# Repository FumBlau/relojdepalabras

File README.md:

# relojdepalabras
nuestro wordclock, de sobremesa o de pared

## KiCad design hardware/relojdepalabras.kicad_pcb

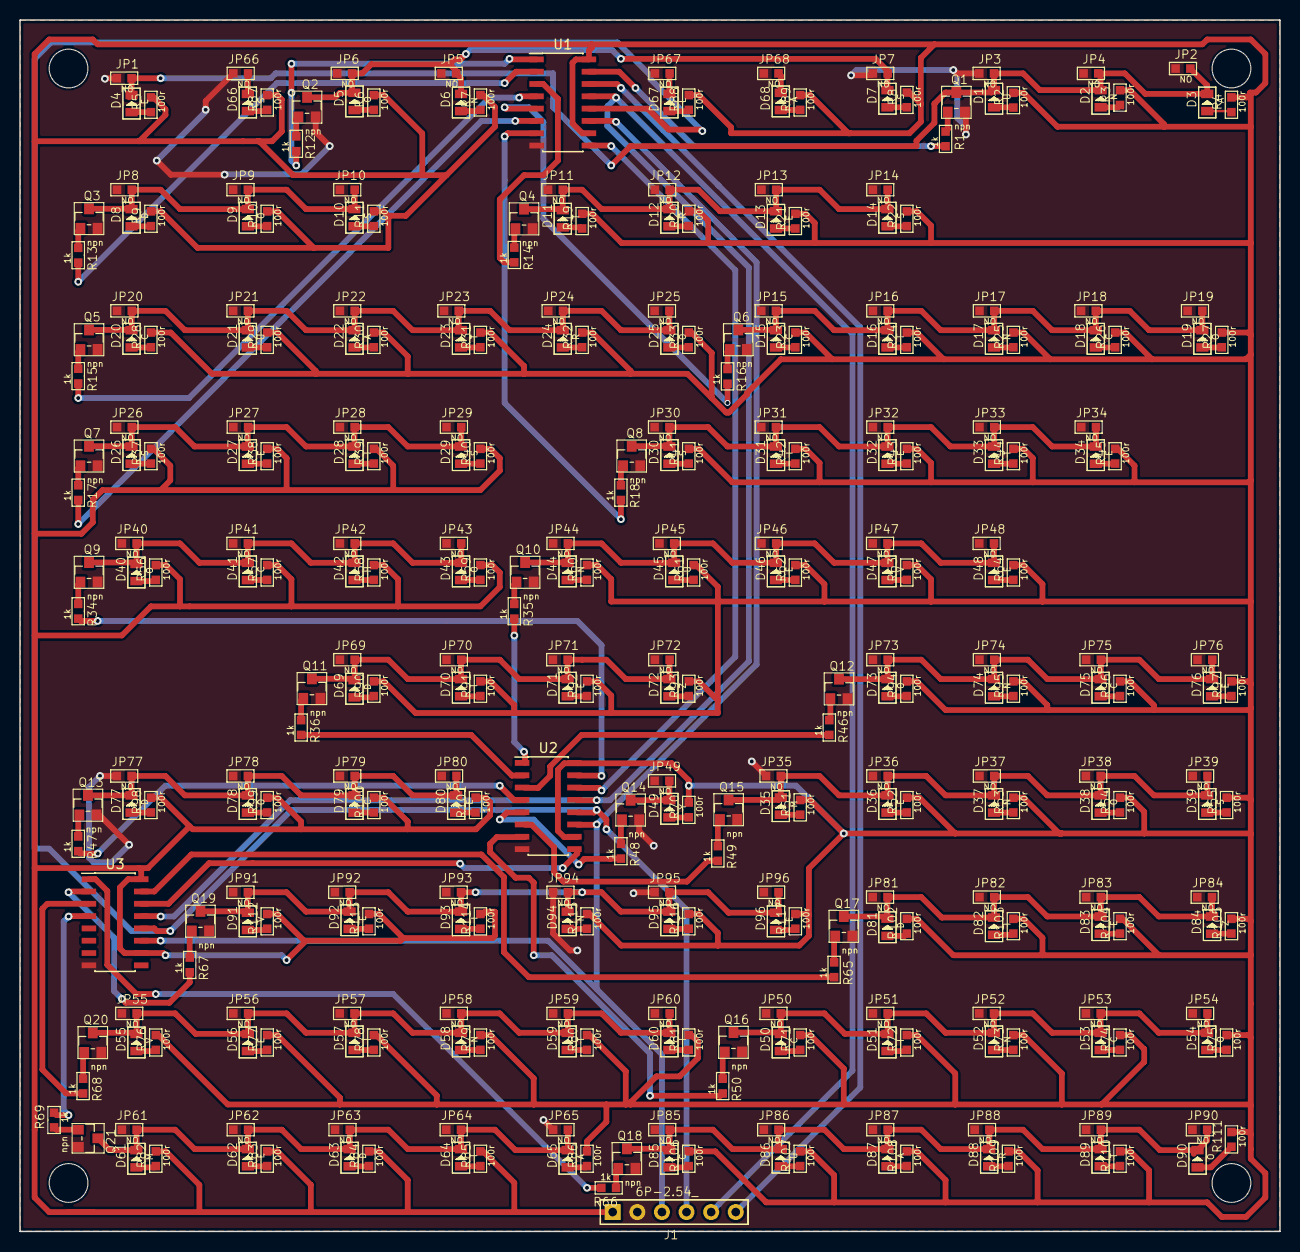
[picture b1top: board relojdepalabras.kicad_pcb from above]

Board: 2 copper layers, 130.0 x 125.0 mm, 334 parts (0 on the bottom side), 170 nets.

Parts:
D1, D21, D45, D86: U; LED-0805
D2, D6, D17, D37, D44, D52, D58, D74, D94: N; LED-0805
D3, D22, D65, D68, D87: A; LED-0805
D4, D13, D27, D32, D34, D36, D46, D48, D56, D62, D71, D76, D80, D83, D92, D96: E; LED-0805
D5, D9, D19, D25, D38, D40, D43, D54, D73, D78, D90: O; LED-0805
D7, D10, D14, D26, D29, D30, D39, D66: S; LED-0805
D8, D63, D69, D77, D81: D; LED-0805
D11, D23, D33, D59, D89, D95: T; LED-0805
D12, D24, D88: R; LED-0805
D15, D18, D20, D41, D50, D53, D75, D79, D85: C; LED-0805
D16, D28, D31, D51, D57, D60, D64, D70, D82, D93: I; LED-0805
D35, D61: M; LED-0805
D42: H; LED-0805
D47, D55, D91: V; LED-0805
D49: Y; LED-0805
D67: L; LED-0805
D72, D84: Z; LED-0805
J1: 6P-2.54_; H6-2.54
JP1, JP2, JP3, JP4, JP5, JP6, JP7, JP8, JP9, JP10, JP11, JP12, JP13, JP14, JP15, JP16, JP17, JP18, JP19, JP20, JP21, JP22, JP23, JP24, JP25, JP26, JP27, JP28, JP29, JP30, JP31, JP32, JP33, JP34, JP35, JP36, JP37, JP38, JP39, JP40, JP41, JP42, JP43, JP44, JP45, JP46, JP47, JP48, JP49, JP50, JP51, JP52, JP53, JP54, JP55, JP56, JP57, JP58, JP59, JP60, JP61, JP62, JP63, JP64, JP65, JP66, JP67, JP68, JP69, JP70, JP71, JP72, JP73, JP74, JP75, JP76, JP77, JP78, JP79, JP80, JP81, JP82, JP83, JP84, JP85, JP86, JP87, JP88, JP89, JP90, JP91, JP92, JP93, JP94, JP95, JP96: NO; R0603
Q1, Q2, Q3, Q4, Q5, Q6, Q7, Q8, Q9, Q10, Q11, Q12, Q13, Q14, Q15, Q16, Q17, Q18, Q19, Q20, Q21: npn; SOT-23
R1, R12, R13, R14, R15, R16, R17, R18, R34, R35, R36, R46, R47, R48, R49, R50, R65, R66, R67, R68, R69: 1k; R0603
R2, R3, R4, R5, R6, R7, R8, R9, R10, R11, R19, R20, R21, R22, R23, R24, R25, R26, R27, R28, R29, R30, R31, R32, R33, R37, R38, R39, R40, R41, R42, R43, R44, R45, R51, R52, R53, R54, R55, R56, R57, R58, R59, R60, R61, R62, R63, R64, R70, R71, R72, R73, R74, R75, R76, R77, R78, R79, R80, R81, R82, R83, R84, R85, R86, R87, R88, R89, R90, R91, R92, R93, R94, R95, R96, R97, R98, R99, R100, R101, R102, R103, R104, R105, R106, R107, R108, R109, R110, R111, R112, R113, R114, R115, R116, R117: 100r; R0603
U1, U2, U3: 74HC595; SOIC-16_3.9x9.9mm_Pitch1.27mm

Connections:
+5V: J1.1, R2.1, R3.1, R4.1, R5.1, R6.1, R7.1, R8.1, R9.1, R10.1, R11.1, R19.1, R20.1, R21.1, R22.1, R23.1, R24.1, R25.1, R26.1, R27.1, R28.1, R29.1, R30.1, R31.1, R32.1, R33.1, R37.1, R38.1, R39.1, R40.1, R41.1, R42.1, R43.1, R44.1, R45.1, R51.1, R52.1, R53.1, R54.1, R55.1, R56.1, R57.1, R58.1, R59.1, R60.1, R61.1, R62.1, R63.1, R64.1, R70.1, R71.1, R72.1, R73.1, R74.1, R75.1, R76.1, R77.1, R78.1, R79.1, R80.1, R81.1, R82.1, R83.1, R84.1, R85.1, R86.1, R87.1, R88.1, R89.1, R90.1, R91.1, R92.1, R93.1, R94.1, R95.1, R96.1, R97.1, R98.1, R99.1, R100.1, R101.1, R102.1, R103.1, R104.1, R105.1, R106.1, R107.1, R108.1, R109.1, R110.1, R111.1, R112.1, R113.1, R114.1, R115.1, R116.1, R117.1, U1.10, U1.16, U2.10, U2.16, U3.10, U3.16
/!sh/ld: J1.4, U1.12, U2.12, U3.12
/datos: J1.6, U1.14
/enable: J1.5, U1.13, U2.13, U3.13
/reloj: J1.3, U1.11, U2.11, U3.11
CINCO: D15.-, D16.-, D17.-, D18.-, D19.-, JP15.1, JP16.1, JP17.1, JP18.1, JP19.1, Q6.3
CUATRO: D20.-, D21.-, D22.-, D23.-, D24.-, D25.-, JP20.1, JP21.1, JP22.1, JP23.1, JP24.1, JP25.1, Q5.3
DIEZ: D69.-, D70.-, D71.-, D72.-, JP69.1, JP70.1, JP71.1, JP72.1, Q11.3
DOCE: D77.-, D78.-, D79.-, D80.-, JP77.1, JP78.1, JP79.1, JP80.1, Q13.3
DOS: D8.-, D9.-, D10.-, JP8.1, JP9.1, JP10.1, Q3.3
E/UNA: D1.-, D2.-, D3.-, D4.-, JP1.1, JP2.1, JP3.1, JP4.1, Q1.3
GND: J1.2, JP1.2, JP2.2, JP3.2, JP4.2, JP5.2, JP6.2, JP7.2, JP8.2, JP9.2, JP10.2, JP11.2, JP12.2, JP13.2, JP14.2, JP15.2, JP16.2, JP17.2, JP18.2, JP19.2, JP20.2, JP21.2, JP22.2, JP23.2, JP24.2, JP25.2, JP26.2, JP27.2, JP28.2, JP29.2, JP30.2, JP31.2, JP32.2, JP33.2, JP34.2, JP35.2, JP36.2, JP37.2, JP38.2, JP39.2, JP40.2, JP41.2, JP42.2, JP43.2, JP44.2, JP45.2, JP46.2, JP47.2, JP48.2, JP49.2, JP50.2, JP51.2, JP52.2, JP53.2, JP54.2, JP55.2, JP56.2, JP57.2, JP58.2, JP59.2, JP60.2, JP61.2, JP62.2, JP63.2, JP64.2, JP65.2, JP66.2, JP67.2, JP68.2, JP69.2, JP70.2, JP71.2, JP72.2, JP73.2, JP74.2, JP75.2, JP76.2, JP77.2, JP78.2, JP79.2, JP80.2, JP81.2, JP82.2, JP83.2, JP84.2, JP85.2, JP86.2, JP87.2, JP88.2, JP89.2, JP90.2, JP91.2, JP92.2, JP93.2, JP94.2, JP95.2, JP96.2, Q1.2, Q2.2, Q3.2, Q4.2, Q5.2, Q6.2, Q7.2, Q8.2, Q9.2, Q10.2, Q11.2, Q12.2, Q13.2, Q14.2, Q15.2, Q16.2, Q17.2, Q18.2, Q19.2, Q20.2, Q21.2, U1.8, U2.8, U3.8
MENOS: D35.-, D36.-, D37.-, D38.-, D39.-, JP35.1, JP36.1, JP37.1, JP38.1, JP39.1, Q15.3
NUEVE: D44.-, D45.-, D46.-, D47.-, D48.-, JP44.1, JP45.1, JP46.1, JP47.1, JP48.1, Q10.3
unnamed: D1.+, R2.2
unnamed: D2.+, R3.2
unnamed: D3.+, R4.2
unnamed: D4.+, R5.2
unnamed: D5.+, R6.2
unnamed: D6.+, R7.2
unnamed: D7.+, R8.2
unnamed: D8.+, R9.2
unnamed: D9.+, R10.2
unnamed: D10.+, R11.2
unnamed: D11.+, R19.2
unnamed: D12.+, R20.2
unnamed: D13.+, R21.2
unnamed: D14.+, R22.2
unnamed: D15.+, R23.2
unnamed: D16.+, R24.2
unnamed: D17.+, R25.2
unnamed: D18.+, R26.2
unnamed: D19.+, R27.2
unnamed: D20.+, R28.2
unnamed: D21.+, R29.2
unnamed: D22.+, R30.2
unnamed: D23.+, R31.2
unnamed: D24.+, R32.2
unnamed: D25.+, R33.2
unnamed: D26.+, R37.2
unnamed: D27.+, R38.2
unnamed: D28.+, R39.2
unnamed: D29.+, R40.2
unnamed: D30.+, R41.2
unnamed: D31.+, R42.2
unnamed: D32.+, R43.2
unnamed: D33.+, R44.2
unnamed: D34.+, R45.2
unnamed: D35.+, R51.2
unnamed: D36.+, R52.2
unnamed: D37.+, R53.2
unnamed: D38.+, R54.2
unnamed: D39.+, R55.2
unnamed: D40.+, R56.2
unnamed: D41.+, R57.2
unnamed: D42.+, R58.2
unnamed: D43.+, R59.2
unnamed: D44.+, R60.2
unnamed: D45.+, R61.2
unnamed: D46.+, R62.2
unnamed: D47.+, R63.2
unnamed: D48.+, R64.2
unnamed: D49.+, R70.2
unnamed: D50.+, R71.2
unnamed: D51.+, R72.2
unnamed: D52.+, R73.2
unnamed: D53.+, R74.2
unnamed: D54.+, R75.2
unnamed: D55.+, R76.2
unnamed: D56.+, R77.2
unnamed: D57.+, R78.2
unnamed: D58.+, R79.2
unnamed: D59.+, R80.2
unnamed: D60.+, R81.2
unnamed: D61.+, R82.2
unnamed: D62.+, R83.2
unnamed: D63.+, R84.2
unnamed: D64.+, R85.2
unnamed: D65.+, R86.2
unnamed: D66.+, R87.2
unnamed: D66.-, JP66.1
unnamed: D67.+, R88.2
unnamed: D67.-, JP67.1
unnamed: D68.+, R89.2
unnamed: D68.-, JP68.1
unnamed: D69.+, R90.2
unnamed: D70.+, R91.2
unnamed: D71.+, R92.2
unnamed: D72.+, R93.2
unnamed: D73.+, R94.2
unnamed: D74.+, R95.2
unnamed: D75.+, R96.2
unnamed: D76.+, R97.2
unnamed: D77.+, R98.2
unnamed: D78.+, R99.2
unnamed: D79.+, R100.2
unnamed: D80.+, R101.2
unnamed: D81.+, R102.2
unnamed: D82.+, R103.2
unnamed: D83.+, R104.2
unnamed: D84.+, R105.2
unnamed: D85.+, R106.2
unnamed: D86.+, R107.2
unnamed: D87.+, R108.2
unnamed: D88.+, R109.2
unnamed: D89.+, R110.2
unnamed: D90.+, R111.2
unnamed: D91.+, R112.2
unnamed: D92.+, R113.2
unnamed: D93.+, R114.2
unnamed: D94.+, R115.2
unnamed: D95.+, R116.2
unnamed: D96.+, R117.2
unnamed: Q1.1, R1.2
unnamed: Q2.1, R12.2
unnamed: Q3.1, R13.2
unnamed: Q4.1, R14.2
unnamed: Q5.1, R15.2
unnamed: Q6.1, R16.2
unnamed: Q7.1, R17.2
unnamed: Q8.1, R18.2
unnamed: Q9.1, R34.2
unnamed: Q10.1, R35.2
unnamed: Q11.1, R36.2
unnamed: Q12.1, R46.2
unnamed: Q13.1, R47.2
unnamed: Q14.1, R48.2
unnamed: Q15.1, R49.2
unnamed: Q16.1, R50.2
unnamed: Q17.1, R65.2
unnamed: Q18.1, R66.2
unnamed: Q19.1, R67.2
unnamed: Q20.1, R68.2
unnamed: Q21.1, R69.2
unnamed: R1.1, U1.15
unnamed: R12.1, U1.1
unnamed: R13.1, U1.2
unnamed: R14.1, U1.3
unnamed: R15.1, U1.4
unnamed: R16.1, U1.5
unnamed: R17.1, U1.6
unnamed: R18.1, U1.7
unnamed: R34.1, U2.15
unnamed: R35.1, U2.1
unnamed: R36.1, U2.2
unnamed: R46.1, U2.3
unnamed: R47.1, U2.4
unnamed: R48.1, U2.5
unnamed: R49.1, U2.6
unnamed: R50.1, U2.7
unnamed: R65.1, U3.15
unnamed: R66.1, U3.1
unnamed: R67.1, U3.2
unnamed: R68.1, U3.3
unnamed: R69.1, U3.4
unnamed: U1.9, U2.14
unnamed: U2.9, U3.14
OCHO: D40.-, D41.-, D42.-, D43.-, JP40.1, JP41.1, JP42.1, JP43.1, Q9.3
ONCE: D73.-, D74.-, D75.-, D76.-, JP73.1, JP74.1, JP75.1, JP76.1, Q12.3
SEIS: D26.-, D27.-, D28.-, D29.-, JP26.1, JP27.1, JP28.1, JP29.1, Q7.3
SIETE: D30.-, D31.-, D32.-, D33.-, D34.-, JP30.1, JP31.1, JP32.1, JP33.1, JP34.1, Q8.3
SonLas: D5.-, D6.-, D7.-, JP5.1, JP6.1, JP7.1, Q2.3
TRES: D11.-, D12.-, D13.-, D14.-, JP11.1, JP12.1, JP13.1, JP14.1, Q4.3
Y: D49.-, JP49.1, Q14.3
cincom: D50.-, D51.-, D52.-, D53.-, D54.-, JP50.1, JP51.1, JP52.1, JP53.1, JP54.1, Q16.3
cuarto: D85.-, D86.-, D87.-, D88.-, D89.-, D90.-, JP85.1, JP86.1, JP87.1, JP88.1, JP89.1, JP90.1, Q18.3
diezm: D81.-, D82.-, D83.-, D84.-, JP81.1, JP82.1, JP83.1, JP84.1, Q17.3
media: D61.-, D62.-, D63.-, D64.-, D65.-, JP61.1, JP62.1, JP63.1, JP64.1, JP65.1, Q21.3
veinte: D91.-, D92.-, D93.-, D94.-, D95.-, D96.-, JP91.1, JP92.1, JP93.1, JP94.1, JP95.1, JP96.1, Q19.3
veinti: D55.-, D56.-, D57.-, D58.-, D59.-, D60.-, JP55.1, JP56.1, JP57.1, JP58.1, JP59.1, JP60.1, Q20.3

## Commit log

2017-06-02 Primera versión del sch, con piezas Seeed
2017-06-06 colocaion de componentes y perimetros de pcb
2017-06-07 primera version de pcb
2017-06-07 limpio archivos
2017-06-07 agujeros de montaje metrica 4
